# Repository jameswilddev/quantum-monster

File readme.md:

# Quantum Monster

## Documentation

- [Assembly Instructions](./docs/assembly-instructions.md)
- [Hardware Design Notes](./docs/hardware-design-notes.md)

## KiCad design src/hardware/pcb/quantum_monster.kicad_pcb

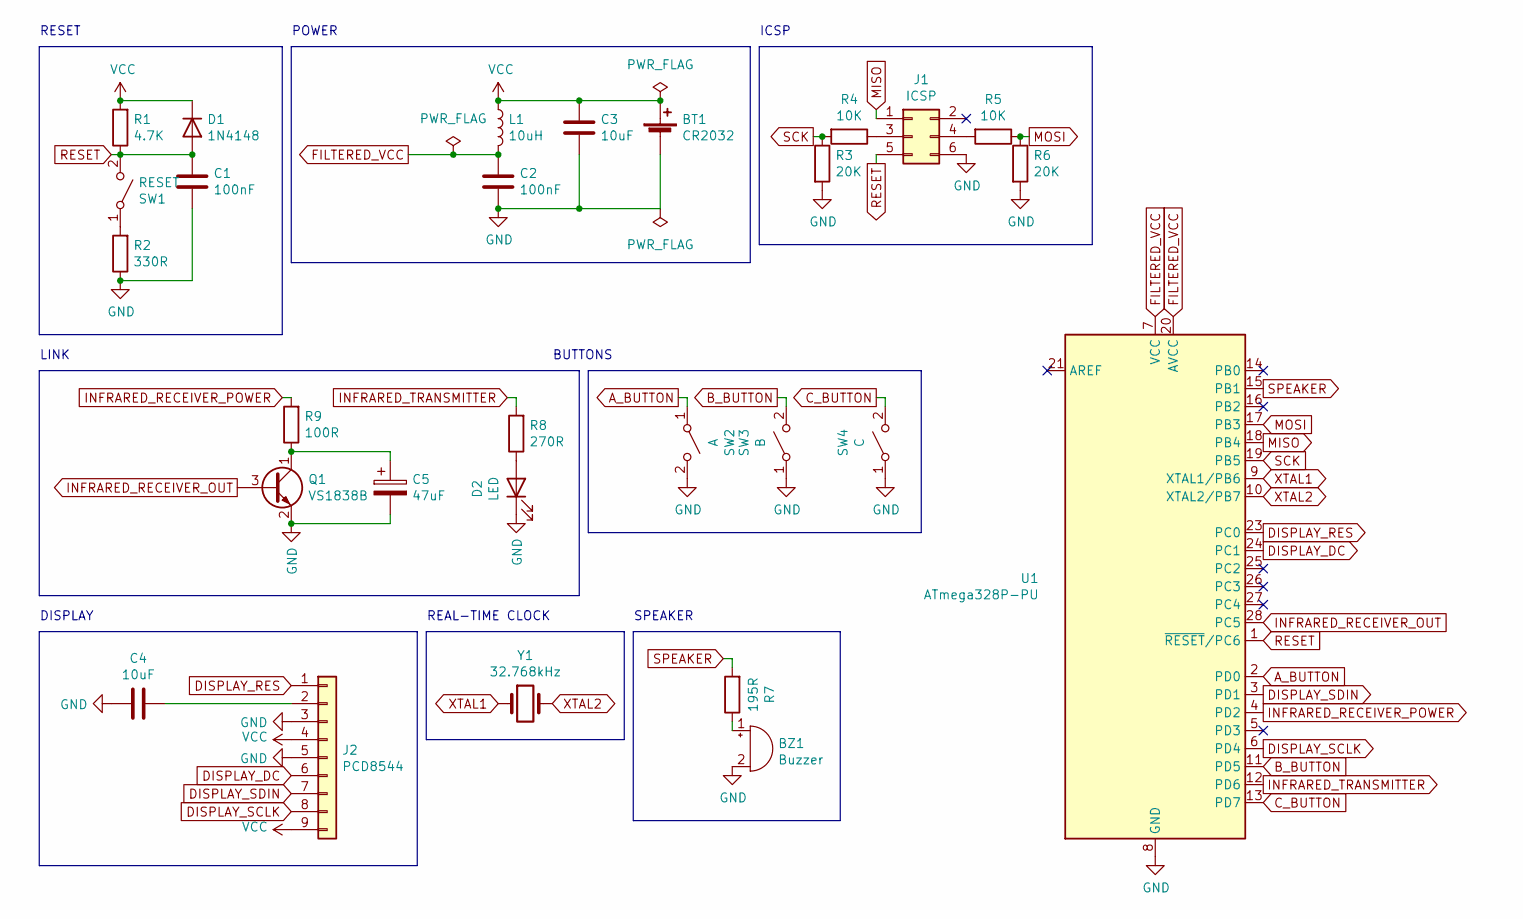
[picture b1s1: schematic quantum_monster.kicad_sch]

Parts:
BT1: CR2032
BZ1: Buzzer; MagneticBuzzer_PUI_AT-0927-TT-6-R
C1, C2: 100nF; C_Disc_D5.0mm_W2.5mm_P2.50mm
C3, C4: 10uF; C_Disc_D4.3mm_W1.9mm_P5.00mm
C5: 47uF; CP_Radial_D5.0mm_P2.00mm
D1: 1N4148; D_DO-34_SOD68_P7.62mm_Horizontal
D2: LED; LED_D5.0mm_IRBlack
J1: ICSP; PinHeader_2x03_P2.54mm_Vertical
J2: PCD8544
L1: 10uH; L_Axial_L5.3mm_D2.2mm_P7.62mm_Horizontal_Vishay_IM-1
Q1: VS1838B; TO-92L_Inline_Wide
R1: 4.7K; R_Axial_DIN0204_L3.6mm_D1.6mm_P7.62mm_Horizontal
R2: 330R; R_Axial_DIN0204_L3.6mm_D1.6mm_P7.62mm_Horizontal
R3, R6: 20K; R_Axial_DIN0204_L3.6mm_D1.6mm_P7.62mm_Horizontal
R4, R5: 10K; R_Axial_DIN0204_L3.6mm_D1.6mm_P7.62mm_Horizontal
R7: 195R; R_Axial_DIN0204_L3.6mm_D1.6mm_P7.62mm_Horizontal
R8: 270R; R_Axial_DIN0204_L3.6mm_D1.6mm_P7.62mm_Horizontal
R9: 100R; R_Axial_DIN0204_L3.6mm_D1.6mm_P7.62mm_Horizontal
SW1: RESET; SW_TH_Tactile_Omron_B3F-10xx
SW2: A; SW_TH_Tactile_Omron_B3F-10xx
SW3: B; SW_TH_Tactile_Omron_B3F-10xx
SW4: C; SW_TH_Tactile_Omron_B3F-10xx
U1: ATmega328P-PU; DIP-28_W7.62mm
Y1: 32.768kHz; Crystal_C38-LF_D3.0mm_L8.0mm_Vertical

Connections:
A_BUTTON: SW2.1 (A), U1.2 (PD0)
B_BUTTON: SW3.2 (B), U1.11 (PD5)
C_BUTTON: SW4.2 (B), U1.13 (PD7)
DISPLAY_DC: J2.6, U1.24 (PC1)
DISPLAY_RES: J2.1, U1.23 (PC0)
DISPLAY_SCLK: J2.8, U1.6 (PD4)
DISPLAY_SDIN: J2.7, U1.3 (PD1)
FILTERED_VCC: C2.1, L1.2, U1.7 (VCC), U1.20 (AVCC)
GND: BT1.2 (-), BZ1.2 (+), C1.2, C2.2, C3.2, C4.2, C5.2, D2.1 (K), J1.6, J2.3, J2.5, Q1.2 (E), R2.1, R3.2, R6.2, SW2.2 (B), SW3.1 (A), SW4.1 (A), U1.8 (GND), U1.22 (GND)
INFRARED_RECEIVER_OUT: Q1.3 (B), U1.28 (PC5)
INFRARED_RECEIVER_POWER: R9.2, U1.4 (PD2)
INFRARED_TRANSMITTER: R8.2, U1.12 (PD6)
MISO: J1.1, U1.18 (PB4)
MOSI: R5.1, R6.1, U1.17 (PB3)
unnamed: BZ1.1 (-), R7.1
unnamed: C4.1, J2.2
unnamed: C5.1, Q1.1 (C), R9.1
unnamed: D2.2 (A), R8.1
unnamed: J1.3, R4.1
unnamed: J1.4, R5.2
unnamed: R2.2, SW1.1 (A)
RESET: C1.1, D1.2 (A), J1.5, R1.1, SW1.2 (B), U1.1 (~RESET/PC6)
SCK: R3.1, R4.2, U1.19 (PB5)
SPEAKER: R7.2, U1.15 (PB1)
VCC: BT1.1 (+), C3.1, D1.1 (K), J2.4, J2.9, L1.1, R1.2
XTAL1: U1.9 (XTAL1/PB6), Y1.1
XTAL2: U1.10 (XTAL2/PB7), Y1.2

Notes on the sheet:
DISPLAY
RESET
ICSP
BUTTONS
REAL-TIME CLOCK
SPEAKER
POWER
LINK

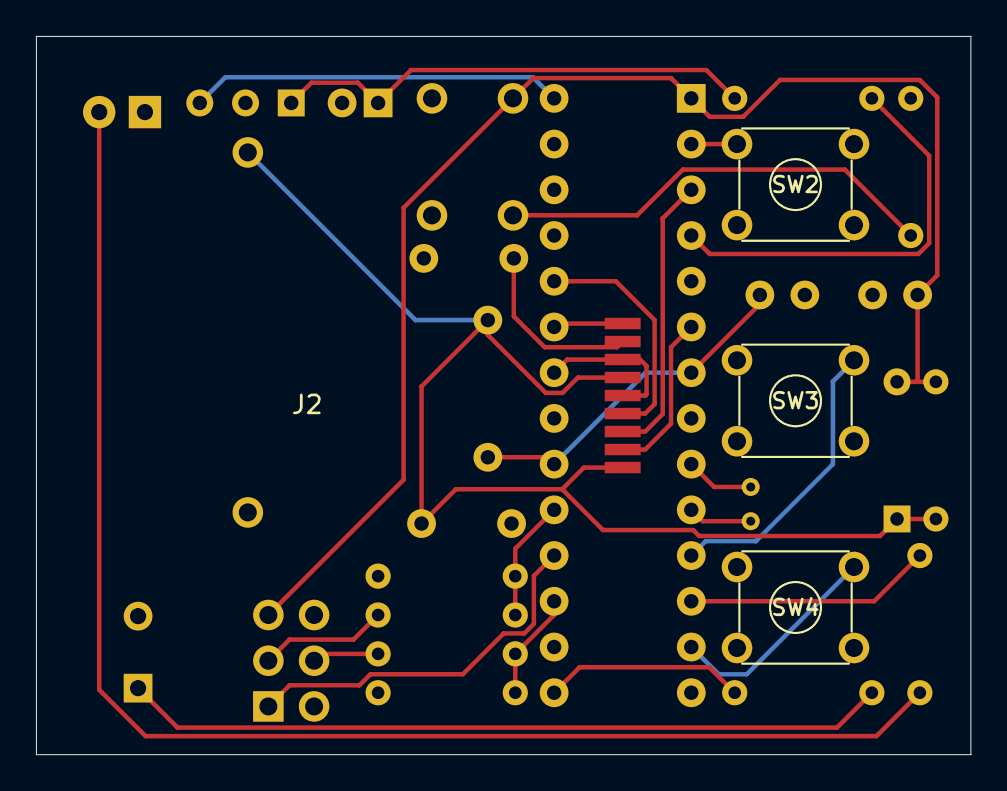
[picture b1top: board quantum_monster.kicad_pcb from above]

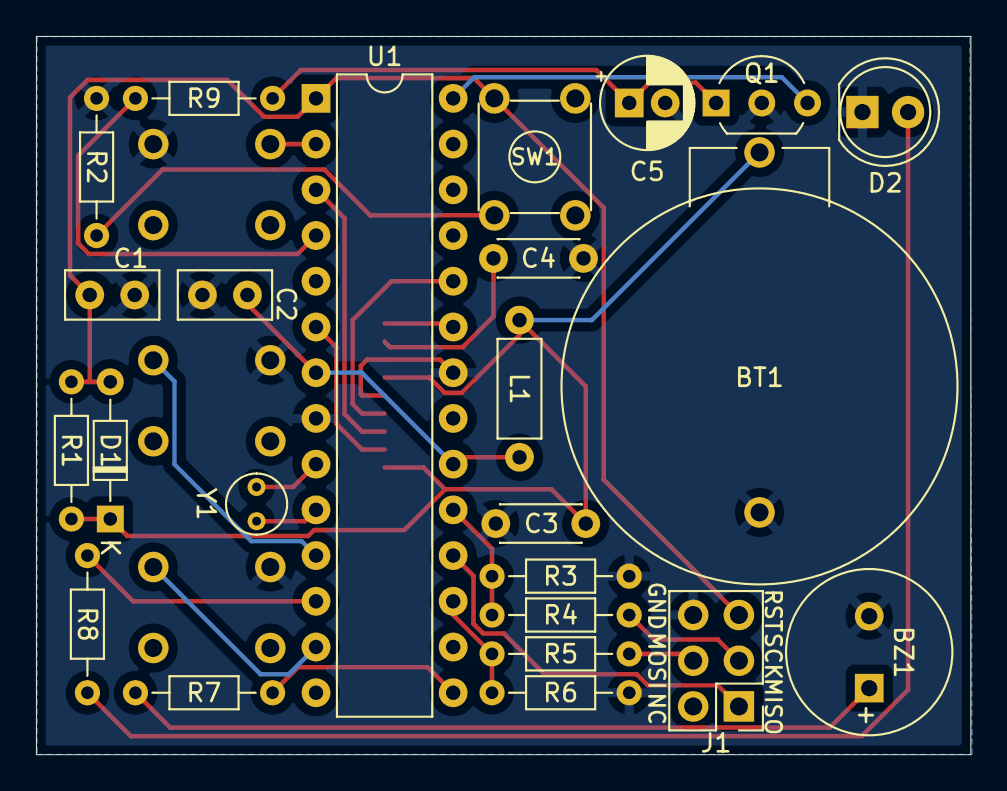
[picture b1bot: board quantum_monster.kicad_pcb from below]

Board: 2 copper layers, 51.9 x 39.9 mm, 28 parts (24 on the bottom side), 27 nets.

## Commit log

2021-12-28 Rename.
2021-12-28 Begin documentation.
2021-12-28 Fix broken link.
2021-12-29 Add renovate.json
2022-01-01 Add placeholders for new sections.
2022-01-01 Fill out simplifications section.
2022-01-01 Break down documentation.
2022-01-01 Rename project.
2022-01-01 Begin structuring project.
2022-01-01 Fix misplaced script.
2022-01-01 Fix speaker build problems.
2022-01-01 Fix main build problems.
2022-01-02 Continue experimenting with hardware design.
2022-01-02 Ignore make outputs.
2022-01-02 Exclude a temporary file.
2022-01-02 Flip LCD.
2022-01-03 Fix typos.
2022-01-03 Start adding shell measurements.
2022-01-03 Begin a total redesign of the software.
2022-01-03 Rework design notes.
2022-01-03 Move all PCB designs under a subdirectory.
2022-01-04 Re-design RTC.
2022-01-04 Extern.
2022-01-06 Fix typing of display pixels.
2022-01-06 Remove erroneous duplicate.
2022-01-06 Add missing variable.
2022-01-06 Work-in-progress AVR target.
2022-01-06 Placeholder assembly instructions.
2022-01-06 Add library placeholder.
2022-01-06 Update makefile.
2022-01-08 Specify initial pixel state.
2022-01-08 Redesign speaker API to work with frequencies rather than timer values.
2022-01-08 Define pixel aspect ratio.
2022-01-08 Add screw measurements.
2022-01-08 Take PCB and display measurements for a LCD test board.
2022-01-08 Model front shell for LCD test.
2022-01-08 WIP display.
2022-01-08 Fill out stubbed macros.
2022-01-08 Fix pull ups not pulling up.
2022-01-08 Fix incorrect assignment.
2022-01-08 WIP speaker.
2022-01-08 Add a logo.
2022-01-08 Add STB submodule.
2022-01-08 Add example images.
2022-01-08 Exclude generated files.
2022-01-08 Add declaration for static data.
2022-01-08 Adjust cropping.
2022-01-08 Add solid sprites.
2022-01-08 Continue developing sprite library.
2022-01-08 Move to declarations.
2022-01-08 Fix VS Code not excluding nested files.
2022-01-08 Remove placeholder.
2022-01-12 Move speaker to timer 1.
2022-01-12 Continue PCB design.
2022-01-13 A complete rethink of the software.
2022-01-14 Fix extern implementations.
2022-01-14 Install missing dependency.
2022-01-14 Add another missing dependency.
2022-01-14 Fix path.
2022-01-16 Adjust PCB outline to allow room for display retainer.
2022-01-16 Continue building out the shell.
2022-01-19 Increase button cap gap.
2022-01-20 Reduce PCB size.
2022-01-20 Add missing include.
2022-01-20 Thicken the display bezel to make the button area thicker.
2022-01-20 Adjust screw measurements.
2022-01-20 Halve PCB back clearance.
2022-01-20 Fix the back not having cutouts.
2022-01-20 Add an initial draft of a thicker wall.
2022-01-22 Begin layout changes to accommodate correct display dimensions.
2022-01-22 Add TODO.
2022-01-22 Update measurements to match updated display.
2022-01-22 Remove display clip.
2022-01-22 Add a spacer between the PCB and display.
2022-01-22 Redesign the infrared cutout.
2022-01-22 Upgrade to KiCad 6.
2022-01-22 Initial KiBot migration.
2022-01-22 Update config.
2022-01-22 Initial production prototype of PCB.
2022-01-22 Fix mispositioned corner cuts.
2022-01-22 Update button positions to match PCB.
2022-01-22 Update infrared cutout position.
2022-01-22 Add a keychain cutout to the wall.
2022-01-22 Update pin mapping.
2022-01-22 Attempted CI fix.
2022-01-22 Work-in-progress sprite conversion.
2022-01-22 Add PCB model.
2022-01-22 Make clean now deletes all generated files.
2022-01-22 Fix invalid header name.
2022-01-22 Add dummy rule contents; makefile appears to be optimizing out.
2022-01-22 Fix broken code generation.
2022-01-22 Fix code generation warnings.
2022-01-22 Fix incorrect sprite.
2022-01-22 Implement remaining image conversions.
2022-01-22 Fix submodules not being cloned.
2022-01-22 Ensure that Aseprite is installed.
2022-01-22 Update INTI-CMNB/KiBot action to v1
2022-01-22 Specify bit order.
2022-01-22 Add framebuffer argument.
2022-01-23 Fix out-of-order display addressing.
2022-01-23 Fix column counts divisible by 8 being rounded up.
2022-01-25 Add static data.
2022-01-27 Thicken the plate and embed the screws deeper.
2022-01-28 Milliseconds -> delay.
2022-01-28 Add a header for errors.
2022-01-30 Add math library.
2022-01-30 Namespace.
2022-01-30 Fix misnamed constants.
2022-01-30 Mark error as not returning.
2022-01-30 Stub error implementation.
2022-01-30 Add helper to round up.
2022-02-02 Adjust button properties.
2022-02-02 Increase plate thickness to allow for deeper screws.
2022-02-02 Deepen screws.
2022-02-02 Reduce screw size.
2022-02-04 Rebuild shell.
2022-02-04 Begin experimenting with a Windows implementation.
2022-02-04 Fix incorrect size.
2022-03-01 Update actions/checkout action to v3
2022-03-25 Update INTI-CMNB/KiBot action to v2
